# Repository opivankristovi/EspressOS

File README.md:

# EspressOS

**Turn a $5 ESP32 into a little PLC you program by drag and drop, straight from your browser.**

Remember Siemens LOGO!? You drop AND gates, timers and counters on a sheet, draw wires, press a button, and your relays start doing things. EspressOS brings that to the ESP32. Flash it once over USB and the board serves its own editor over Wi-Fi. There's nothing to install, no Arduino IDE, and no compile-and-upload loop. Open `http://espressos.local`, wire up your logic, press **Deploy**, and watch it run live.

<sub>A greenhouse controller running live: temperature opens the vent, low humidity opens the mister, a night timer runs the path lights, and the grow light dims as sunlight increases.</sub>

## Why you'll like it

- **Programs in minutes, not compile cycles.** Changes take effect the moment you press Deploy. A bad program is rejected and the old one keeps running. **Restore** throws away your edits and brings back what's on the board, and before a deploy replaces a program, EspressOS offers to save a copy of it.
- **See your logic think.** Wires glow green when high, analog values ride along the wires, and timers count down inside their blocks, just like LOGO!'s online test.
- **Sensors without code.** Scan the I²C bus, click the BME280 it found, and drop a *Sensor value* block. Temperature, humidity, pressure, light, voltage and 1-Wire temperature work out of the box. A *generic I²C register* reader covers many other chips.
- **A control panel for free.** Add web switches, push buttons and setpoints to your program, and they show up as controls on the Live panel, from any phone on your network.
- **Talks to Home Assistant.** *MQTT in* and *MQTT out* blocks connect your logic to any MQTT broker, and web switches, push buttons and setpoints appear in Home Assistant on their own through MQTT discovery.
- **Try it before you solder.** With no board connected, the same engine runs as a simulator in your browser. Click inputs to toggle them and watch the outputs respond.
- **Built like a controller, not a toy.** Fixed 10 ms scan cycle on its own CPU core, outputs released to a safe state on stop or redeploy, a watchdog, and the program kept in flash across power cycles.
- **Speaks IEC 61131-3.** Export to PLCopen XML for OpenPLC, Beremiz and other IEC tools, and import their FBD programs.
- **Updates over the air.** New firmware or web UI uploads from the Settings page.

<table>
<tr>
<td width="68%"></td>
<td width="32%"></td>
</tr>
<tr>
<td><sub>Click any block to tune it: thresholds, delays, pins, names. Light and dark themes follow your system.</sub></td>
<td><sub>The Live panel: switches, buttons, output lamps and sensor values.</sub></td>
</tr>
</table>

## The block library

| Category | Blocks |
|---|---|
| **Inputs & outputs** | Digital input, digital output (with active-low option), analog input, PWM output, constant, web switch / push button, web setpoint |
| **Logic** | AND, OR, NOT, NAND, NOR, XOR, SR latch, edge detect |
| **Timers & counters** | On-delay, off-delay, pulse, blinker, weekly timer (NTP clock), up/down counter |
| **Analog** | Compare, threshold with hysteresis, math (+ − × ÷ min max), scale, select |
| **Sensors** | BME280, SHT3x, BH1750, ADS1115, DS18B20, generic I²C register |
| **MQTT** | MQTT in (value and on/off from a topic), MQTT out (publishes a value when it changes) |

## Get started

**Just curious?** Clone the repo and run the editor against a simulated board, no hardware needed:

```bash
npm run mock
```

Then open http://localhost:8080 and import [`examples/greenhouse.json`](examples/greenhouse.json) (or its PLCopen version [`greenhouse.xml`](examples/greenhouse.xml)) from **Settings → Import**, or open http://localhost:8080/?sim for the in-browser simulator.

**Have an ESP32?** You need [PlatformIO](https://platformio.org/) (`pip install platformio`) and an ESP32 dev board (ESP32-WROOM, 4 MB).

```bash
python tools/build_web.py
```

```bash
cd firmware && pio run -t upload && pio run -t uploadfs
```

1. The board starts a Wi-Fi network called `EspressOS-XXXX`. Join it and the setup page opens (or browse to `192.168.4.1`).
2. **Choose an admin password** (the board accepts no programs until you do), and optionally enter your Wi-Fi details. The board restarts and joins your network.
3. Open `http://espressos.local`, log in as `admin`, and start dragging blocks.

Pin notes: I²C defaults to SDA 21 / SCL 22 (changeable in Settings); while a program uses I²C sensors, those two pins can't also be inputs or outputs. GPIO 0, 1 and 3 (boot and serial) and 6–11 (wired to flash) are never offered. GPIO 34–39 are input-only. Analog inputs use ADC1 pins, since ADC2 is unavailable while Wi-Fi is on. The board itself checks all of this on every deploy, so a program from a file can't slip a bad pin past it.

## How it works

```
Browser ──HTTP/WebSocket──► ESP32
  editor + simulator           ├─ web server: UI from LittleFS (gzipped, ~56 KB)
  (web/)                       ├─ REST API  /api/program, /api/run, /api/stop, /api/vin, /api/i2c/scan, /api/config, /api/ota
                               ├─ WebSocket /ws  live values, 4×/s
                               ├─ engine task (core 1): scan cycle every 10 ms
                               ├─ sensor task (core 0): polls sensors, caches values
                               └─ MQTT task (core 0): broker connection, Home Assistant discovery
```

A program is plain JSON: blocks, wires `[fromId, fromPort, toId, toPort]` and sensor devices. You can version it in git or share it like the [greenhouse example](examples/greenhouse.json). On deploy the board validates it and sorts the blocks so each runs after its inputs. Feedback loops are allowed and read the previous cycle's value, as on a PLC.

**Run and Stop behave like a PLC.** Stop releases every output (pins go high-impedance, so active-high and active-low relay boards both drop out). Run restarts the program from a clean state: timers, counters and latches reset, and outputs are set up again at their *off* level, so active-low relays never glitch on.

**Security.** The board drives real outputs, so the web API is locked down:
- An admin password is required before the board accepts any program. It is stored as a salted SHA-256 hash, and changes take effect immediately. After 5 wrong passwords, the address that sent them is locked out for 30 seconds, doubling with every further miss.
- Every request is checked *before* the board touches flash or allocates memory. That includes firmware uploads, which the web server library streams before its own auth middleware runs.
- Writes must carry an `X-EOS` header and a matching `Origin`. A web page from another site can't send that header without a CORS preflight, which the board never approves, so such pages can't switch relays. API calls under a foreign `Host` name are refused, which blocks DNS rebinding.
- Request bodies over 64 KB, or of unknown size (chunked), are refused. Settings that could brick the board, like I²C or 1-Wire on flash pins, are rejected.
- After a power cut, the board keeps retrying your router for 2 minutes before opening its own `EspressOS-XXXX` network, so you can still reach it. It closes that network again once the router is back. Only the very first setup network is open; once an admin password exists, it uses WPA2 with a random key that **Settings** shows you. Note it down.
- Settings and the program are saved atomically, with a backup copy, so a power cut while saving can't corrupt them. If the settings were ever unreadable anyway, the board refuses all logins rather than falling back to the open first-setup mode; erase it over USB to start over.
- Firmware updates accept only a real firmware image or web UI image. Any other file is refused, so picking the wrong `.bin` can't wipe the web interface.

Known limits: HTTP Basic auth over plain HTTP, so use it on a network you trust. The Wi-Fi and MQTT passwords are stored readably, because the board needs them to connect, and MQTT runs without TLS. Firmware images aren't signed; ESP32 secure boot and flash encryption are the proper fix for both.

**Adding a sensor driver.** The ESP32 can't compile code itself, so drivers are built into the firmware. To add one, write a small class in `firmware/src/Sensors.cpp`, list it in `DRIVERS` in `web/js/catalog.js`, rebuild, and upload `firmware.bin` from **Settings → Firmware update**. Until then, the generic I²C block handles many simple chips.

## MQTT and Home Assistant

Enter your broker under **Settings → MQTT & Home Assistant**: host or IP, port, and a user name and password if the broker needs them. If you run Home Assistant, its Mosquitto add-on is the usual broker. Changes apply at once, without a reboot, and the status line shows whether the board is connected.

**MQTT in** subscribes to a topic. Its `#` output is the value of the last message: `ON`, `true`, `open`, `yes` and `PRESS` count as 1, `OFF`, `false`, `closed` and `no` as 0, and anything else must be a number. Its `Q` output is on while that value is 0.5 or more. Until the first message arrives, the block outputs the value you set. **MQTT out** publishes its input whenever the formatted value changes, as a number (with the decimals you choose), `ON`/`OFF`, `true`/`false` or `1`/`0`. It sends at most once per interval (1 s by default), but always ends on the latest value, and it retains the message by default so new subscribers get the current state. Topics can't contain the wildcards `+` or `#`, and a program can use up to 16 topics in each direction.

Every web control is also an MQTT topic under the base topic, which is `espressos/<hostname>` unless you set another:

| Topic | Direction | Payload |
|---|---|---|
| `<base>/vN` | board → broker (retained) | `ON`/`OFF` for switches and buttons, the number for setpoints |
| `<base>/vN/set` | broker → board | `ON`/`OFF`, `PRESS` (a short press of a push button), or a number (clamped to the setpoint's range) |
| `<base>/status` | board → broker (retained) | `online`, or `offline` (the broker's last will) |

`N` is the web control's slot. With **Home Assistant discovery** on (the default), each web switch shows up as a switch entity, each push button as a button entity and each setpoint as a number slider, all grouped under one device named after the board. Deploying a program updates the entities; web controls you delete are removed from Home Assistant too.

## IEC 61131-3 / OpenPLC interoperability

**Settings → Export PLCopen XML** writes your program as a PLCopen TC6 XML (v2.01) file with a Function Block Diagram. OpenPLC Editor, Beremiz and other IEC 61131-3 tools can open it. **Settings → Import** reads such files back, both EspressOS exports and FBD programs made elsewhere.

| EspressOS block | IEC 61131-3 |
|---|---|
| AND / OR / XOR / NOT | `AND` / `OR` / `XOR` / `NOT` |
| NAND / NOR | `AND` / `OR` with a negated output |
| Latch (reset wins / set wins) | `RS` / `SR` |
| Edge detect | `R_TRIG` + `F_TRIG` |
| On-delay / Off-delay / Pulse | `TON` / `TOF` / `TP` |
| Counter | `CTUD` (import also takes `CTU`) |
| Compare / Math / Select | `GT` `GE` `LT` `LE` `EQ` `NE` / `ADD` `SUB` `MUL` `DIV` `MIN` `MAX` / `SEL` |
| Digital in / out | variables at `%IX0.n` / `%QX0.n` |
| Analog in / PWM out | `%IWn` / `%QWn` through `EOS_AI` / `EOS_AO` (0–65535 like OpenPLC) |
| Blinker, Threshold, Scale, Weekly timer | `EOS_BLINK`, `EOS_THRESH`, `EOS_SCALE`, `EOS_WEEK`, written in Structured Text and included in the file |
| Web switch / setpoint, Sensor value | plain variables (`V0_…`, `S_…`) |
| MQTT in / MQTT out | plain variables (`MQ_…` and `MQ_…_Q` / `MQO_…`) |

Feedback loops are routed through a variable, which gives the same one-cycle delay. GPIO pins, block numbers and sensor settings travel in the file's `addData` section, so an exported program imports back unchanged.

When importing a file from another tool:
- Located variables become I/O blocks. EspressOS assigns GPIO pins itself and lists them for you to check.
- Internal variables become wires, and literals become block settings.
- Variables that are only ever read become web controls.
- Unsupported parts are listed instead of silently dropped: Ladder, ST or SFC bodies, `CTD` semantics, `LD` load inputs, and `ET` elapsed-time outputs.

Limits:
- OpenPLC sets ESP32 pins per board, so after exporting, copy the I/O table the export shows into OpenPLC's board settings.
- Sensors, MQTT and the weekly timer's clock have no IEC equivalent. They're exported as variables you connect in your PLC (`S_…`, `MQ_…`, `MQO_…`, `CLOCK_DOW` / `CLOCK_MINUTE`). Weekly timers stay off until you also set `CLOCK_VALID`, just like EspressOS keeps them off until its clock is synced.
- The PWM frequency of an analog output isn't exported; OpenPLC uses its board's own.
- Inverted digital inputs and outputs are exported as `NOT` blocks, because OpenPLC ignores inversion marks on variables. EspressOS folds them back in when you re-import.

Every push runs the [IEC check](.github/workflows/iec.yml) on GitHub Actions:
1. Export the [examples](examples/) and validate them against the official PLCopen schema.
2. Convert them to Structured Text with OpenPLC Editor's own generator, and compile the result with OpenPLC's `matiec` compiler and `gcc`, exactly as OpenPLC does before uploading to a board.
3. Run the compiled programs for 3,000 scan cycles on random inputs (switches, analog values, sensors, MQTT messages, the clock) next to EspressOS's engine, and check that every output matches on every cycle.

## Development

| What | Command |
|---|---|
| Editor against a fake board | `npm run mock`, then open http://localhost:8080 (starts in first-run setup mode; add `-- --configured` to skip it) |
| Pure simulator | open http://localhost:8080/?sim |
| JS engine + PLCopen tests | `npm test` (set `PLCOPEN_XSD` to OpenPLC/Beremiz's `tc6_xml_v201.xsd` and install `lxml` to also validate exports against the schema) |
| C++ engine tests | `cd firmware && pio test -e native` (needs a host g++) |
| Bundle the UI for the board | `npm run build:web` |
| Export programs to PLCopen XML | `node tools/export_plcopen.js <out-dir> examples/*.json` |
| Compile exports with OpenPLC's toolchain and compare behaviour | runs in CI ([`iec.yml`](.github/workflows/iec.yml)); `tools/iec_behaviour.js` builds the test harness |

[`ci.yml`](.github/workflows/ci.yml) runs the JS and C++ tests and builds the firmware and web UI image on every push.

The engine is implemented twice: in C++ for the board (`firmware/lib/engine`) and in JS for the simulator (`web/js/sim.js`). Both run the same test cases, and `tools/test_sim.js` checks that the block tables in `Blocks.cpp`, `sim.js` and `catalog.js` stay in sync.

## Status

EspressOS is young. Two self-reviews found 29 issues across security, controller behaviour, IEC export and the interface, and all have been fixed. Tested on every push:
- C++ engine: 17 tests. JS engine: 20 tests.
- PLCopen import/export: 9 tests, including schema validation and checking that a program behaves the same after export and re-import.
- OpenPLC: the exports compile with `matiec` and behave the same as in EspressOS.
- The firmware build: 1.64 MB of the 1.9 MB app slot.

The complete editor flow is tested by hand against the mock board and the simulator.

**Runs on real hardware.** EspressOS has been flashed to an ESP32 dev board (ESP32-D0WD-V3, CH340 USB). It booted cleanly, went through the setup page, joined the home Wi-Fi and served the editor. A deployed program then switched the on-board LED (GPIO 2) live from a web switch, analog inputs read a joystick's position, and a PWM output dimmed the LED from both a web setpoint and the joystick. The board stayed cool throughout. A firmware update over Wi-Fi rebooted the board with its program intact, and uploading the wrong `.bin` (`partitions.bin`) was refused with an error. Connected to a Home Assistant MQTT broker, web switches and setpoints showed up in Home Assistant almost instantly and could be operated from there. Not yet tried on hardware: sensor drivers, the fallback network after a router outage, and the MQTT in / MQTT out blocks. Reports from other boards are very welcome.

On the roadmap: Modbus RTU and UART blocks, an HTTP request block, MQTT over TLS, CI-built `.bin` releases you can flash from the browser, and retentive (power-fail-safe) counters.

## License

MIT, see [LICENSE](LICENSE).

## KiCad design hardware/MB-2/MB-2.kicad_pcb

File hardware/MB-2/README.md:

# MB-2: sensor node, 4 precise analog in, 6 touch, 4 relay channels (rev A, design)

MB-2 is a carrier board for a plugged-in **ESP32 DOIT DevKit V1 (30-pin)**. It is the hardware that the `eos-mb2` board profile in [web/js/boards.js](../../web/js/boards.js) describes. Where MB-1 is a controller with mains outputs, MB-2 is a monitoring node: precise analog inputs, capacitive touch, sensor buses, and a header that drives an external relay module. There is no mains voltage on MB-2.

**Status:** design agreed; the `eos-mb2` profile and the firmware's touch support are in place; schematic done (generated, netlist-checked, ERC clean); PCB placed and routed (generated, DRC: no errors); Gerbers and a 3D model for the enclosure. Nothing ordered or built yet.

## Design decisions

| Topic | Choice | Why |
|---|---|---|
| Module | ESP32 DOIT DevKit V1, 30-pin, in two 1×15 female headers (rows 25.4 mm apart) | Swappable; programming and serial console over the DevKit's own USB. No ESP32 or USB-serial on MB-2. |
| Power | 12–24 V DC terminal, *and* the DevKit's USB | Either works. The board's switching regulator feeds the DevKit's VIN through a diode, so both can be connected at once. Relays run only from 12–24 V. |
| Regulator | Traco TSR 1-2450E (5 V 1 A switching, SIP-3, 7–36 V in) | Efficient (about 90 %) and hand-solderable; a linear regulator would burn about 4 W at 24 V. |
| Analog in | 4 × 0–10 V or 4–20 mA, on an ADS1115 16-bit ADC (breakout module in a socket) | Far more accurate than the ESP32 ADC; ADS1115 is already supported by the firmware. A jumper per input selects 4–20 mA. |
| Extra inputs | GPIO 34, 35, 36, 39 as four 0–3.3 V analog/digital inputs | These ADC pins have no touch sensor, so they become plain inputs. |
| Touch | 6 capacitive touch inputs, GPIO 13, 14, 15, 27, 32, 33 | All touch-capable pins on the 30-pin DevKit except 4 (1-Wire) and the boot straps 2 and 12. Needs a new touch block in the firmware (part of this work). |
| Relays | No relays on MB-2: a 6-pin header for a common 5 V 4-channel relay module, each input driven by a MOSFET | Keeps mains off the board. The MOSFETs pull the module's active-low inputs, so any 5 V module switches reliably and nothing clicks while the ESP32 boots. |
| Buses | I2C (GPIO 21/22) on a terminal and a Qwiic socket; 1-Wire (GPIO 4) on a terminal | As MB-1. |
| Spare GPIO | IO1–IO3 on GPIO 23, 25, 26 (in, out, PWM) | The remaining free, non-strapping pins. |
| Build | Fully hand-soldered: 0805 passives, SOT-23 and SMA/SMB diodes, through-hole terminals and headers | No assembly order needed. |
| Enclosure | Bare board, 120 × 80 mm, four M3 holes; a 3D model for designing a case | As MB-1. |

## Pin map (must match the `eos-mb2` profile)

| GPIO | DevKit pin | Terminal | Profile uses | Circuit |
|---|---|---|---|---|
| 36 (VP) | left 2 | IN1 | ai, di | 1 kΩ series, clamp to 3V3/GND, 100 nF |
| 39 (VN) | left 3 | IN2 | ai, di | same |
| 34 | left 4 | IN3 | ai, di | same |
| 35 | left 5 | IN4 | ai, di | same |
| 32 | left 6 | T5 | touch | 1 kΩ series |
| 33 | left 7 | T6 | touch | same |
| 25 | left 8 | IO2 | di, do, pwm | 100 Ω series |
| 26 | left 9 | IO3 | di, do, pwm | 100 Ω series |
| 27 | left 10 | T4 | touch | 1 kΩ series |
| 14 | left 11 | T2 | touch | same (pulses at boot: touch only) |
| 13 | left 13 | T1 | touch | same |
| 15 | right 13 | T3 | touch | same (boot strap: touch only) |
| 23 | right 1 | IO1 | di, do, pwm | 100 Ω series |
| 22 | right 2 | SCL | I2C | 4.7 kΩ to 3V3 |
| 21 | right 5 | SDA | I2C | 4.7 kΩ to 3V3 |
| 19 | right 6 | R4 | do, active high | MOSFET → relay header IN4 |
| 18 | right 7 | R3 | do, active high | MOSFET → IN3 |
| 17 (TX2) | right 9 | R2 | do, active high | MOSFET → IN2 |
| 16 (RX2) | right 10 | R1 | do, active high | MOSFET → IN1 |
| 4 | right 11 | DQ | 1-Wire | 4.7 kΩ to 3V3 |
| 2, 5, 12 | | — | not connected | boot straps / on-board LED (GPIO 2) |
| 1, 3 | | — | serial console (DevKit USB) | |
| VIN | left 15 | — | 5 V in from the regulator, through a Schottky diode | |
| 3V3 | right 15 | — | 3.3 V out of the DevKit's regulator: ADS1115, pull-ups, sensor terminals | |

The four analog inputs AI1–AI4 are not GPIOs: they are channels A0–A3 of the ADS1115 at I2C address 0x48. Programs read them with the *Sensor value* block (ADS1115, channels A0–A3, in volts at the ADC), so they are not profile terminals.

## Terminals

All terminals are low voltage. 3.5 mm pitch screw terminals along the top edge, power (5.08 mm) and the relay header on the left.

| Block | Positions |
|---|---|
| Power (2, 5.08 mm) | +12–24 V · GND |
| Analog (8) | AI1 · AI2 · AI3 · AI4 · +V · +V · GND · GND |
| Inputs (6) | IN1 · IN2 · IN3 · IN4 · 3V3 · GND |
| Touch (7) | T1 · T2 · T3 · T4 · T5 · T6 · GND |
| GPIO (5) | IO1 · IO2 · IO3 · 3V3 · GND |
| I2C (4) | 3V3 · SDA · SCL · GND, plus a Qwiic socket |
| 1-Wire (3) | 3V3 · DQ · GND |
| Relay module (1×6 pin header, 2.54 mm) | GND · IN1 · IN2 · IN3 · IN4 · VCC (5 V) |

**+V** is the 12–24 V supply through a 100 mA PTC, to power 2-wire 4–20 mA transmitters and 0–10 V sensors. The 3V3 positions share a 200 mA PTC.

## Circuits

### Power

* J1 12–24 V in → F1 PTC 1.1 A hold → D1 SS34 Schottky (reverse polarity) → D2 SMAJ30A TVS to GND → C1 47 µF/50 V → U1 TSR 1-2450E → **+5V**, C2 22 µF.
* **+5V** → relay header VCC. Budget: four relay coils about 4 × 75 mA = 300 mA.
* **+5V** → D3 SS14 Schottky → DevKit **VIN**. The diode stops the DevKit's USB from feeding the regulator's output. On USB alone the ESP32 and sensors run but the relay module has no supply.
* **3V3** comes from the DevKit's own regulator (about 500 mA spare after the ESP32). F2 PTC 200 mA feeds the 3V3 terminal positions and the Qwiic socket.
* F3 PTC 100 mA from the 12–24 V rail (after D1) to the **+V** terminals.

### Analog inputs AI1–AI4 (ADS1115)

Per channel: terminal → 30 kΩ 1 % → node → 10 kΩ 1 % to GND; node → 100 nF to GND; node → BAT54S clamp to 3V3/GND; node → ADS1115 A0–A3.

* **0–10 V** (no jumper): 10 V at the terminal = 2.5 V at the ADC, read in volts by the ADS1115 driver (default ±6.144 V range, 0.19 mV per count): about 13 000 counts over 0–10 V.
* **4–20 mA** (jumper JP1–JP4 fitted): the jumper connects a 150 Ω 0.5 W shunt from the terminal to GND. 20 mA gives 3.0 V at the terminal and 0.75 V at the ADC; 4–20 mA spans about 3 200 counts. Burden 3 V, fine for 12 V and 24 V loops.
* **Never fit the jumper with a voltage sensor**: the shunt would load it (a 10 V output into 150 Ω).
* ADS1115: a common 10-pin breakout module (VDD, GND, SCL, SDA, ADDR, ALRT, A0–A3) in a 1×10 female header, powered from 3V3, ADDR to GND (0x48).

### Extra inputs IN1–IN4

Terminal → 1 kΩ → GPIO; BAT54S clamp to 3V3/GND and 100 nF at the pin. 0–3.3 V signals; the clamp survives a short to 24 V for a moment (24 mA through the 1 kΩ) but not continuously.

### Touch T1–T6

Terminal → 1 kΩ → GPIO (ESD limiting). A wire to a metal plate, foil or a pad behind plastic works as the electrode; keep the wires short and away from the relay-module wiring. GND next to them for a shielded cable.

### Relay header R1–R4

GPIO → 100 Ω → gate of Q1–Q4 (2N7002 / AO3400A, SOT-23), 100 kΩ gate to GND; drain → header INn, source → GND. A typical 5 V module (Songle relays, PC817 inputs, active-low) switches on when INn is pulled low: GPIO high = relay on. The 100 kΩ keeps the inputs released while GPIO 16–19 float at reset.

### Buses

* I2C: 4.7 kΩ pull-ups to 3V3 (the ADS1115 module has its own 10 kΩ; together about 3.2 kΩ). Qwiic: JST SM04B-SRSS-TB, GND · 3V3 · SDA · SCL.
* 1-Wire: 4.7 kΩ to 3V3.

## Schematic

[MB-2.kicad\_sch](MB-2.kicad_sch) is the schematic and [MB-2.pdf](MB-2.pdf) a print of it; open [MB-2.kicad\_pro](MB-2.kicad_pro) in KiCad. Like MB-1's, it is **generated**: [gen\_schematic.py](gen_schematic.py) holds every part, value, footprint and the net on each pin, so change the script and generate again rather than editing the sheet.

```bash
python gen_schematic.py
kicad-cli sch erc MB-2.kicad_sch
kicad-cli sch export netlist --format kicadsexpr -o MB-2.net MB-2.kicad_sch
python check_netlist.py MB-2.net
kicad-cli sch export pdf -o MB-2.pdf MB-2.kicad_sch
```

[check\_netlist.py](check_netlist.py) compares the netlist KiCad reads from the sheet with the nets in the script, pin by pin: 62 nets, 0 differences. ERC has no errors; on a KiCad install whose library tables were never set up, `kicad-cli` also lists "library not in the current configuration" warnings.

* **The DevKit** is two 1×15 female headers, J2 (left row) and J3 (right row), pin 1 at the antenna end. Unused DevKit pins (EN, GPIO 12, 2, 5, TX0, RX0) carry no-connect flags.
* **The ADS1115** is a 1×10 female header (J4) for the common breakout module: VDD, GND, SCL, SDA, ADDR (to GND, 0x48), ALRT (unused), A0–A3.
* **Footprints** are the hand-solder versions: 0805 passives, SMA diodes, 1812/1206 PTCs, 1210 shunts, through-hole terminals and headers.

Reference designators on the sheet:

|Function|Refs|
|-|-|
|Power|J1, F1–F3, D1–D3, C1, C2, U1|
|DevKit|J2, J3|
|Analog AI1–AI4|ADS1115 socket J4, series R1–R4 (30k), to GND R5–R8 (10k), C3–C6, clamps D4–D7, jumpers JP1–JP4, shunts R9–R12 (150 Ω), terminal J5|
|Inputs IN1–IN4|R13–R16, C7–C10, clamps D8–D11, terminal J6|
|Touch T1–T6|R17–R22, terminal J7|
|Relay header|gate R23–R26, pull-down R27–R30, MOSFETs Q1–Q4, header J8|
|GPIO, buses|R31–R33, pull-ups R34–R36, terminals J9 (IO), J10 (I2C), J12 (1-Wire), Qwiic J11|

## PCB

[MB-2.kicad\_pcb](MB-2.kicad_pcb): two layers, 120 × 80 mm, four M3 holes, all parts on top. Renders: [top](MB-2-top.png), [bottom](MB-2-bottom.png). Generated and routed by script, like MB-1:

```bash
"%LOCALAPPDATA%\Programs\KiCad\10.0\bin\python.exe" gen_pcb.py
"%LOCALAPPDATA%\Programs\KiCad\10.0\bin\python.exe" route.py
kicad-cli pcb drc MB-2.kicad_pcb
```

* **[gen\_pcb.py](gen_pcb.py)** reads the parts and nets from `gen_schematic.py`, places every footprint and writes the outline, holes, ground pours on both layers, silkscreen and net classes. `gen_pcb.py --silk` redoes only the part fields and silkscreen on a routed board.
* **[route.py](route.py)** is MB-1's: Freerouting (about a minute on this board), then loose vias and stubs removed, ground stitching vias, islands joined, and any track Freerouting necked below the 0.2 mm minimum widened back.

**Layout.**
* **Top edge:** the analog (J5), input (J6) and touch (J7) terminals, wires entering from the top, each terminal's parts in a column underneath it.
* **Analog block:** the 4–20 mA jumpers and their shunts sit left of the analog columns, with the ADS1115 socket (J4) below them.
* **Right:** the DevKit sockets with the antenna pointing right. Pin 1 sits 6 mm from the edge, so the antenna end overhangs the board, and a copper-free strip keeps the board's copper away from it.
* **Left edge:** the relay-module header (J8) with its four MOSFET drivers.
* **Bottom:** the power chain, with power (J1), GPIO (J9), I2C (J10), 1-Wire (J12) and the Qwiic socket along the bottom edge.
* **Under the DevKit:** low SMD parts and tracks; it sits about 8.5 mm up on its sockets.

**Rules** (net classes in the project):

|Net class|Nets|Clearance|Track|
|-|-|-|-|
|Default|signals|0.2 mm|0.3 mm|
|Power|GND, +5V, +3V3, +VS, VIN\_RAW, VIN\_F, VIN\_DK, 3V3\_OUT, VLOOP|0.2 mm|0.6 mm|
|Touch|TCH1–6 (GPIO side), TT1–6 (terminal side)|0.5 mm|0.35 mm|

The Touch class keeps other tracks, and the ground pour on both layers, 0.5 mm away from the touch traces. That lowers the idle capacitance the ESP32 measures, so a finger changes the reading more. The longest touch trace (T4) is 47 mm; T1 and T2 are the shortest. If one pad reads less clearly than the others, it is probably T3 or T4 and its threshold can be set a little higher in the Touch block.

**DRC:** no errors and no unconnected items. The only warnings are "footprint library not in the current configuration" (they go away once KiCad has been started once).

**Before ordering:** print the board at 1:1 and check the DevKit sockets against your DevKit (rows 25.4 mm apart) and the ADS1115 socket against your module's pinout.

## Ordering the board

```bash
"%LOCALAPPDATA%\Programs\KiCad\10.0\bin\python.exe" gerbers.py
```

[gerbers.py](gerbers.py) writes [fab/MB-2-gerbers.zip](fab/MB-2-gerbers.zip): copper, mask, paste and silkscreen on both sides, the outline, and plated and non-plated drill files in mm. Upload it at any PCB fab as a 2-layer, 1.6 mm, 120 × 80 mm board. MB-2 is hand-soldered, so there is no assembly BOM or placement file. The zip was checked against the board: 475 plated holes (383 vias, 92 pads) and 4 non-plated M3 holes, outline 120.00 × 80.00 mm.

## 3D model for an enclosure

```bash
"%LOCALAPPDATA%\Programs\KiCad\10.0\bin\python.exe" make_3d.py
```

[3d/MB-2.stl](3d/MB-2.stl) is the assembled board as one mesh (binary STL, mm) for Fusion, TinkerCAD or any CAD. The origin is the board's lower-left corner with the analog, input and touch terminals at the top; Z runs up from the bottom of the board (top surface at z = 1.6). The Traco regulator and the 1812 fuse have no KiCad model and are blocks from their data sheets. **The plugged-in DevKit and ADS1115 module are envelopes** measured from common boards, since they decide the enclosure's height: check them against your own modules.

|Item|Where (mm)|Height (z, mm)|
|-|-|-|
|Board|0–120 × 0–80, 1.6 thick, 2 mm corner radius|0–1.6|
|Mounting holes, M3 (3.2 mm)|(3.5, 3.5), (116.5, 3.5), (3.5, 76.5), (116.5, 76.5)| |
|Pins and solder below the board|x 2.7–114.3|down to −2.9: standoffs of 5 mm or more|
|ESP32 DevKit (plugged in)|x 73.9–125.4 (antenna end 5.4 mm past the right edge), y 25.2–53.5|10.1–15.0|
|DevKit USB plug|left end of the DevKit, x ≈ 74, y ≈ 39|≈ 11.5–14.5; leave room for the cable|
|ADS1115 module (plugged in)|x 21.4–49.4, y 41.5–59.3|10.1–13.5|
|Power terminal J1 (5.08 mm, tallest part)|x 8.7–20.2, y 1.0–8.6|up to 15.4|
|Bottom terminals J9, J10, J12 (wires in from the bottom edge)|x 21.7–69.3, y 1.0–8.6|up to 10.8|
|Qwiic J11 (opening to the bottom edge)|x 73–79, y 1.5–6.5|up to 4.6|
|Top terminals J5–J7 (wires in from the top edge)|x 8.2–87.2, y 71.4–79.0|up to 10.8|
|Relay-module header J8 (cable to the module)|x 1.7–4.3, y 30–45|up to 10.1|
|Traco regulator U1|x 30.3–38.7, y 13.4–25.5|up to 12.0|

Keep the enclosure non-metallic around the DevKit's antenna end (right edge).

## BOM sketch (to be finalised with the schematic)

| Part | Qty | MPN |
|---|---|---|
| ESP32 DOIT DevKit V1, 30-pin | 1 | (plugged in, not soldered) |
| Female header 1×15, 2.54 mm | 2 | |
| ADS1115 breakout module + female header 1×10 | 1 | |
| Switching regulator 5 V 1 A, SIP-3 | 1 | Traco TSR 1-2450E |
| N-MOSFET SOT-23 | 4 | 2N7002 or AO3400A |
| Schottky 40 V 3 A / 1 A, SMA | 1 / 1 | SS34 / SS14 |
| TVS 30 V, SMA | 1 | Littelfuse SMAJ30A |
| Schottky pair SOT-23 (clamps) | 8 | BAT54S |
| PTC 1.1 A / 200 mA / 100 mA | 1 / 1 / 1 | |
| Resistors 0805 | | 30 k 1 % ×4, 10 k 1 % ×4, 1 k ×10, 100 Ω ×7, 100 k ×4, 4.7 k ×3, 150 Ω 0.5 W (1210) ×4 |
| Capacitors 0805 / electrolytic | | 100 nF ×8, 22 µF, 47 µF 50 V |
| Jumpers 1×2 + shunts | 4 | |
| Screw terminals 3.5 mm | 8+6+7+5+4+3 | |
| Screw terminal 5.08 mm, 2-pos | 1 | |
| Pin header 1×6 male | 1 | |
| Qwiic socket | 1 | JST SM04B-SRSS-TB |

## Firmware and editor support

* **Touch input block** (`TOUCH`): reads a pad with the ESP32's touch sensor. Output Q is on while the raw reading is below the block's threshold (default 30) and goes off again 10 % above it; the second output is the raw reading, to find a good threshold in the live view. In the simulator, click the block to touch it.
* **`touch` terminal use** in board profiles, checked the same way by the editor ([web/js/boards.js](../../web/js/boards.js)) and the firmware (`firmware/lib/engine/src/Board.cpp`): only pins with a touch sensor (GPIO 2, 4, 12–15, 27, 32, 33), and no fixed active level.
* The `eos-mb2` profile replaces an earlier placeholder (8 DI, 2 AI, 4 relays, 2 DC outputs) that no hardware matched.
* Analog inputs AI1–AI4: add an ADS1115 sensor at address 0x48 on the Sensors page and use *Sensor value* blocks. The value is the voltage at the ADC: multiply by 4 for terminal volts, or (V × 4 / 150 × 1000) for mA with the jumper fitted.

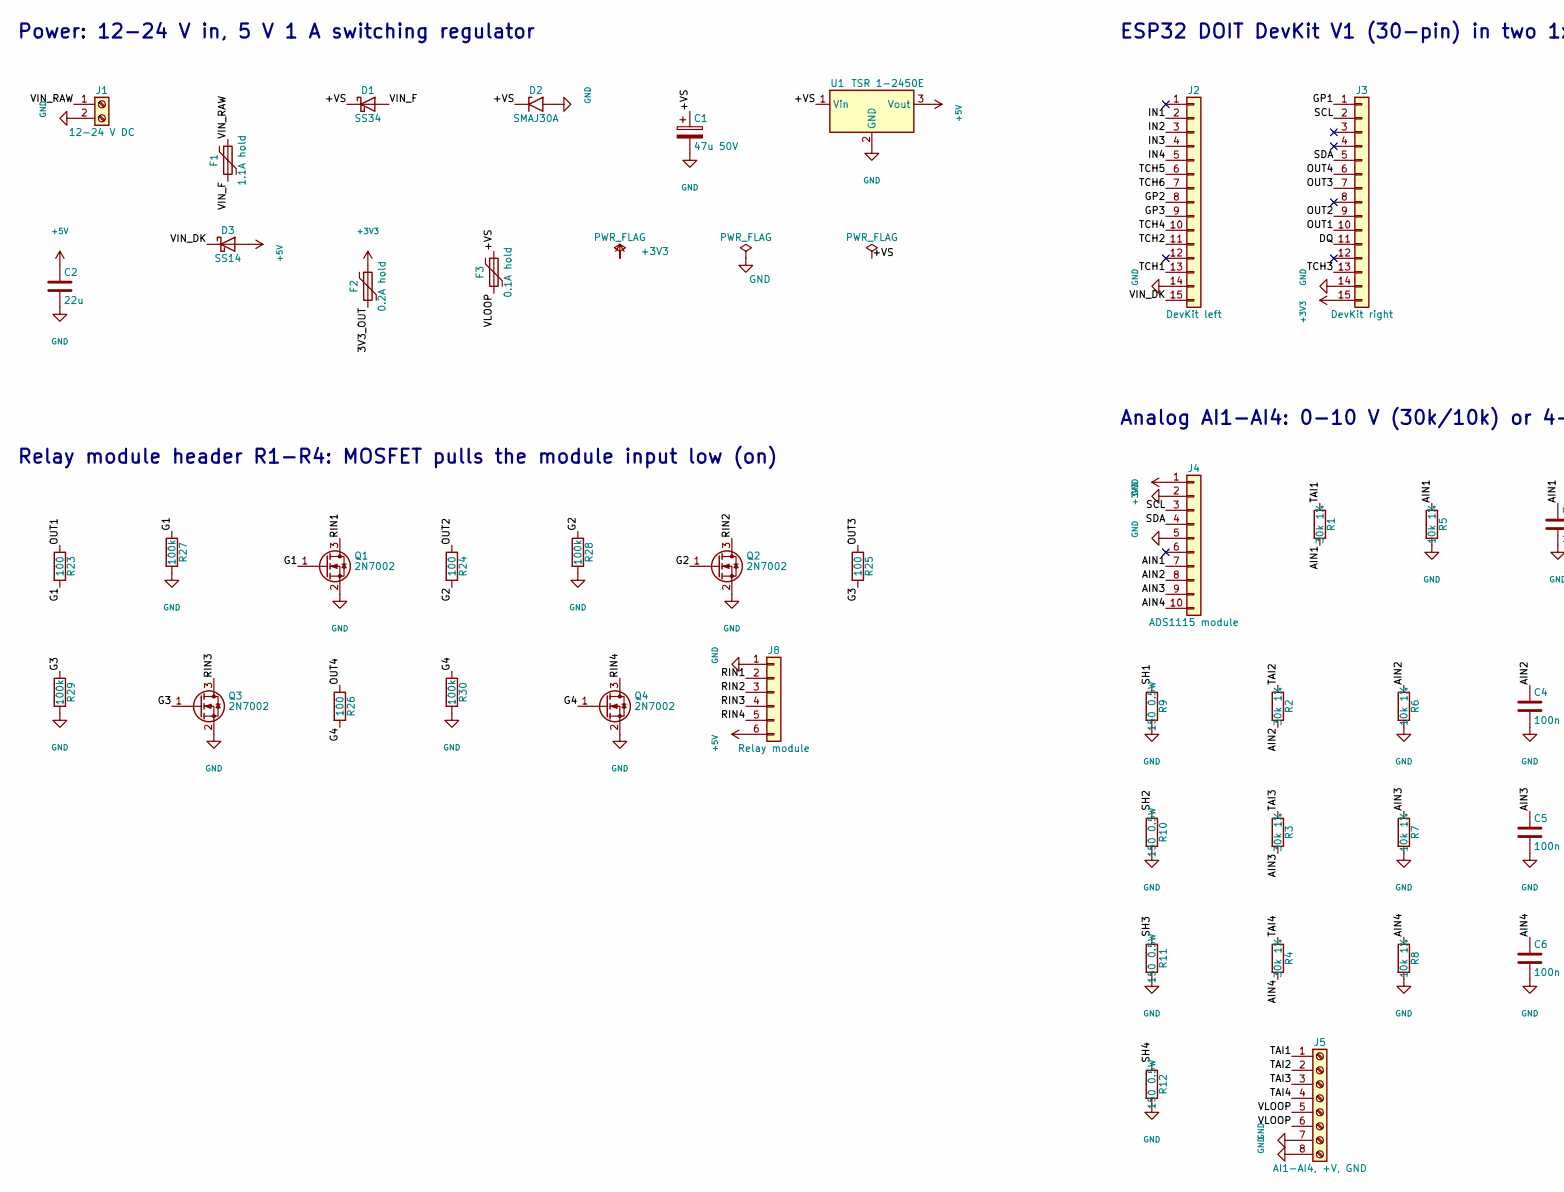
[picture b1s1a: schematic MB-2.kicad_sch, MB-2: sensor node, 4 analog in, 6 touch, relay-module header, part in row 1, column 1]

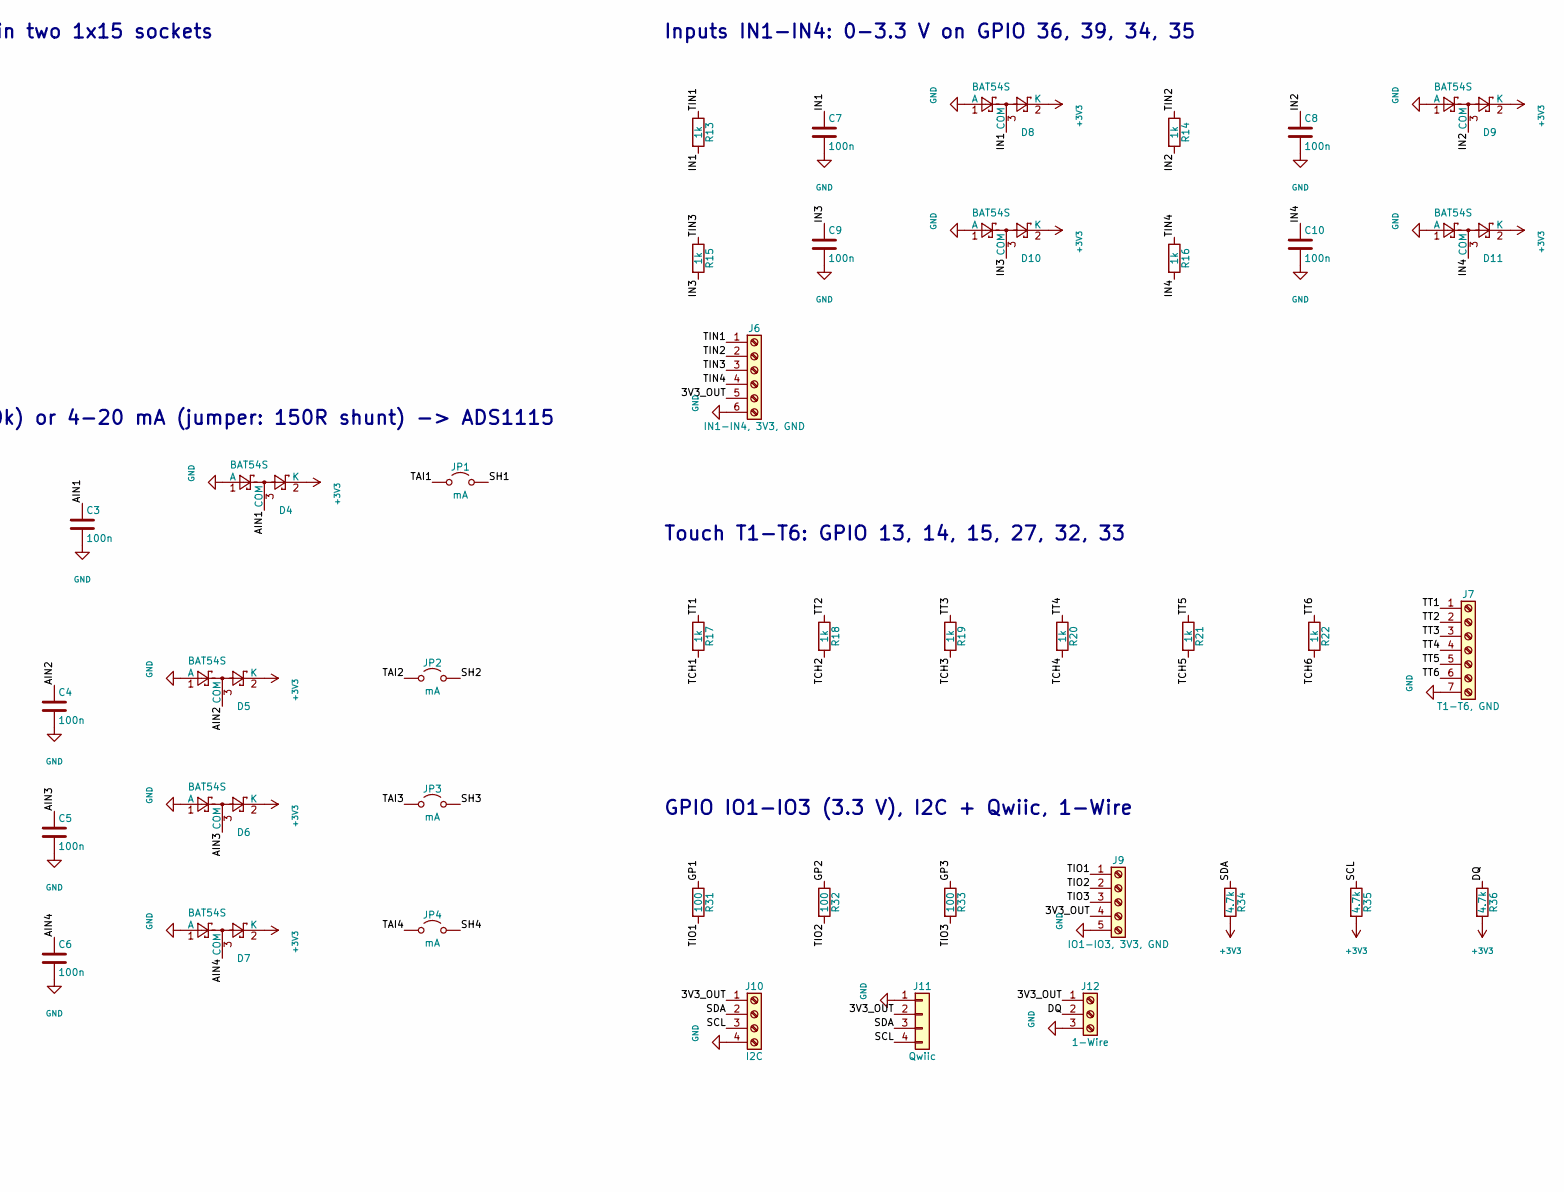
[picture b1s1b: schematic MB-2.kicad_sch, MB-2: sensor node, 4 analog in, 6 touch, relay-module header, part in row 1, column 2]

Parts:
C1: 47u 50V; CP_Elec_6.3x7.7
C2: 22u; C_0805_2012Metric_Pad1.18x1.45mm_HandSolder
C3, C4, C5, C6, C7, C8, C9, C10: 100n; C_0805_2012Metric_Pad1.18x1.45mm_HandSolder
D1: SS34; D_SMA_Handsoldering; MPN SS34 (40 V 3 A Schottky)
D2: SMAJ30A; D_SMA_Handsoldering; MPN Littelfuse SMAJ30A
D3: SS14; D_SMA_Handsoldering; MPN SS14 (40 V 1 A Schottky)
D4, D5, D6, D7, D8, D9, D10, D11: BAT54S; SOT-23
F1: 1.1A hold; Fuse_1812_4532Metric_Pad1.30x3.40mm_HandSolder; MPN Bourns MF-MSMF110-2
F2: 0.2A hold; Fuse_1206_3216Metric_Pad1.42x1.75mm_HandSolder; MPN Bourns MF-NSMF020-2
F3: 0.1A hold; Fuse_1206_3216Metric_Pad1.42x1.75mm_HandSolder; MPN Bourns MF-NSMF010-2
J1: 12-24 V DC; TerminalBlock_Phoenix_MKDS-1,5-2-5.08_1x02_P5.08mm_Horizont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; MPN Phoenix MKDS 1,5/2-5,08 (1715721)
J2: DevKit left; PinSocket_1x15_P2.54mm_Vertical; MPN Female header 1x15, 2.54 mm
J3: DevKit right; PinSocket_1x15_P2.54mm_Vertical; MPN Female header 1x15, 2.54 mm
J4: ADS1115 module; PinSocket_1x10_P2.54mm_Vertical; MPN ADS1115 breakout (VDD GND SCL SDA ADDR 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
J5: AI1-AI4, +V, GND; TerminalBlock_Phoenix_PT-1,5-8-3.5-H_1x08_P3.50mm_Horizontal
J6: IN1-IN4, 3V3, GND; TerminalBlock_Phoenix_PT-1,5-6-3.5-H_1x06_P3.50mm_Horizontal
J7: T1-T6, GND; TerminalBlock_Phoenix_PT-1,5-7-3.5-H_1x07_P3.50mm_Horizontal
J8: Relay module; PinHeader_1x06_P2.54mm_Vertical
J9: IO1-IO3, 3V3, GND; TerminalBlock_Phoenix_PT-1,5-5-3.5-H_1x05_P3.50mm_Horizontal
J10: I2C; TerminalBlock_Phoenix_PT-1,5-4-3.5-H_1x04_P3.50mm_Horizontal
J11: Qwiic; JST_SH_SM04B-SRSS-TB_1x04-1MP_P1.00mm_Horizontal; MPN JST SM04B-SRSS-TB
J12: 1-Wire; TerminalBlock_Phoenix_PT-1,5-3-3.5-H_1x03_P3.50mm_Horizontal
JP1, JP2, JP3, JP4: mA; PinHeader_1x02_P2.54mm_Vertical
Q1, Q2, Q3, Q4: 2N7002; SOT-23
R1, R2, R3, R4: 30k 1%; R_0805_2012Metric_Pad1.20x1.40mm_HandSolder
R5, R6, R7, R8: 10k 1%; R_0805_2012Metric_Pad1.20x1.40mm_HandSolder
R9, R10, R11, R12: 150 0.5W; R_1210_3225Metric_Pad1.30x2.65mm_HandSolder
R13, R14, R15, R16, R17, R18, R19, R20, R21, R22: 1k; R_0805_2012Metric_Pad1.20x1.40mm_HandSolder
R23, R24, R25, R26, R31, R32, R33: 100; R_0805_2012Metric_Pad1.20x1.40mm_HandSolder
R27, R28, R29, R30: 100k; R_0805_2012Metric_Pad1.20x1.40mm_HandSolder
R34, R35, R36: 4.7k; R_0805_2012Metric_Pad1.20x1.40mm_HandSolder
U1: TSR 1-2450E; Converter_DCDC_TRACO_TSR1-xxxxE_THT; MPN Traco TSR 1-2450E

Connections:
3V3_OUT: F2.2, J6.5, J9.4, J10.1, J11.2, J12.1
+3V3: D4.2 (K), D5.2 (K), D6.2 (K), D7.2 (K), D8.2 (K), D9.2 (K), D10.2 (K), D11.2 (K), F2.1, J3.15, J4.1, R34.2, R35.2, R36.2
+5V: C2.1, D3.2 (A), J8.6, U1.3 (Vout)
+VS: C1.1, D1.1 (K), D2.1 (A1), F3.1, U1.1 (Vin)
AIN1: C3.1, D4.3 (COM), J4.7, R1.2, R5.1
AIN2: C4.1, D5.3 (COM), J4.8, R2.2, R6.1
AIN3: C5.1, D6.3 (COM), J4.9, R3.2, R7.1
AIN4: C6.1, D7.3 (COM), J4.10, R4.2, R8.1
DQ: J3.11, J12.2, R36.1
G1: Q1.1 (G), R23.2, R27.1
G2: Q2.1 (G), R24.2, R28.1
G3: Q3.1 (G), R25.2, R29.1
G4: Q4.1 (G), R26.2, R30.1
GND: C1.2, C2.2, C3.2, C4.2, C5.2, C6.2, C7.2, C8.2, C9.2, C10.2, D2.2 (A2), D4.1 (A), D5.1 (A), D6.1 (A), D7.1 (A), D8.1 (A), D9.1 (A), D10.1 (A), D11.1 (A), J1.2, J2.14, J3.14, J4.2, J4.5, J5.7, J5.8, J6.6, J7.7, J8.1, J9.5, J10.4, J11.1, J12.3, Q1.2 (S), Q2.2 (S), Q3.2 (S), Q4.2 (S), R5.2, R6.2, R7.2, R8.2, R9.2, R10.2, R11.2, R12.2, R27.2, R28.2, R29.2, R30.2, U1.2 (GND)
GP1: J3.1, R31.1
GP2: J2.8, R32.1
GP3: J2.9, R33.1
IN1: C7.1, D8.3 (COM), J2.2, R13.2
IN2: C8.1, D9.3 (COM), J2.3, R14.2
IN3: C9.1, D10.3 (COM), J2.4, R15.2
IN4: C10.1, D11.3 (COM), J2.5, R16.2
OUT1: J3.10, R23.1
OUT2: J3.9, R24.1
OUT3: J3.7, R25.1
OUT4: J3.6, R26.1
RIN1: J8.2, Q1.3 (D)
RIN2: J8.3, Q2.3 (D)
RIN3: J8.4, Q3.3 (D)
RIN4: J8.5, Q4.3 (D)
SCL: J3.2, J4.3, J10.3, J11.4, R35.1
SDA: J3.5, J4.4, J10.2, J11.3, R34.1
SH1: JP1.2 (B), R9.1
SH2: JP2.2 (B), R10.1
SH3: JP3.2 (B), R11.1
SH4: JP4.2 (B), R12.1
TAI1: J5.1, JP1.1 (A), R1.1
TAI2: J5.2, JP2.1 (A), R2.1
TAI3: J5.3, JP3.1 (A), R3.1
TAI4: J5.4, JP4.1 (A), R4.1
TCH1: J2.13, R17.2
TCH2: J2.11, R18.2
TCH3: J3.13, R19.2
TCH4: J2.10, R20.2
TCH5: J2.6, R21.2
TCH6: J2.7, R22.2
TIN1: J6.1, R13.1
TIN2: J6.2, R14.1
TIN3: J6.3, R15.1
TIN4: J6.4, R16.1
TIO1: J9.1, R31.2
TIO2: J9.2, R32.2
TIO3: J9.3, R33.2
TT1: J7.1, R17.1
TT2: J7.2, R18.1
TT3: J7.3, R19.1
TT4: J7.4, R20.1
TT5: J7.5, R21.1
TT6: J7.6, R22.1
VIN_DK: D3.1 (K), J2.15
VIN_F: D1.2 (A), F1.2
VIN_RAW: F1.1, J1.1
VLOOP: F3.2, J5.5, J5.6

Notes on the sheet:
Power: 12-24 V in, 5 V 1 A switching regulator
ESP32 DOIT DevKit V1 (30-pin) in two 1x15 sockets
Analog AI1-AI4: 0-10 V (30k/10k) or 4-20 mA (jumper: 150R shunt) -> ADS1115
Inputs IN1-IN4: 0-3.3 V on GPIO 36, 39, 34, 35
Touch T1-T6: GPIO 13, 14, 15, 27, 32, 33
Relay module header R1-R4: MOSFET pulls the module input low (on)
GPIO IO1-IO3 (3.3 V), I2C + Qwiic, 1-Wire

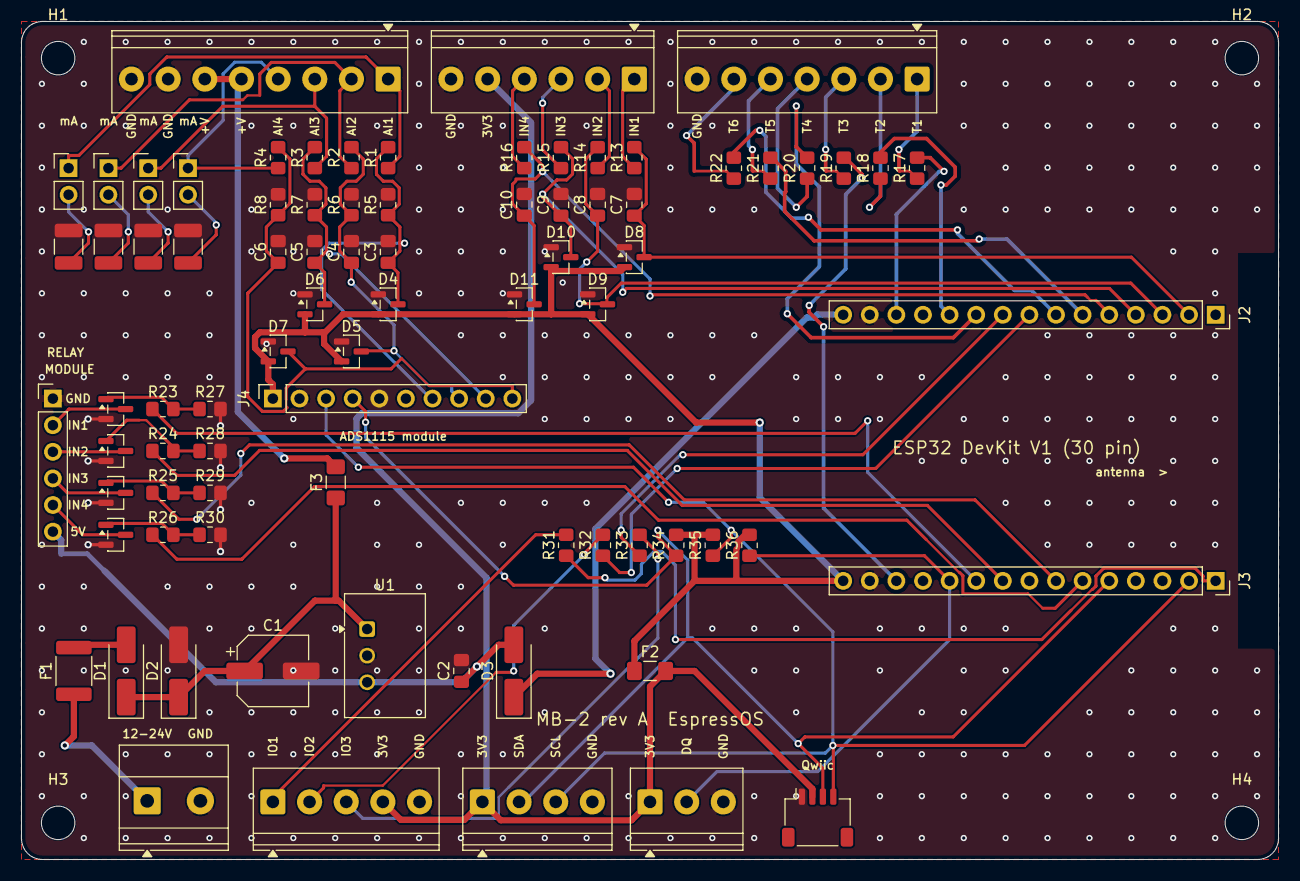
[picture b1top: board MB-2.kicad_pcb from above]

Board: 2 copper layers, 120.0 x 80.0 mm, 85 parts (0 on the bottom side), 62 nets.

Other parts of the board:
H1, H2, H3, H4: MountingHole_3.2mm_M3
